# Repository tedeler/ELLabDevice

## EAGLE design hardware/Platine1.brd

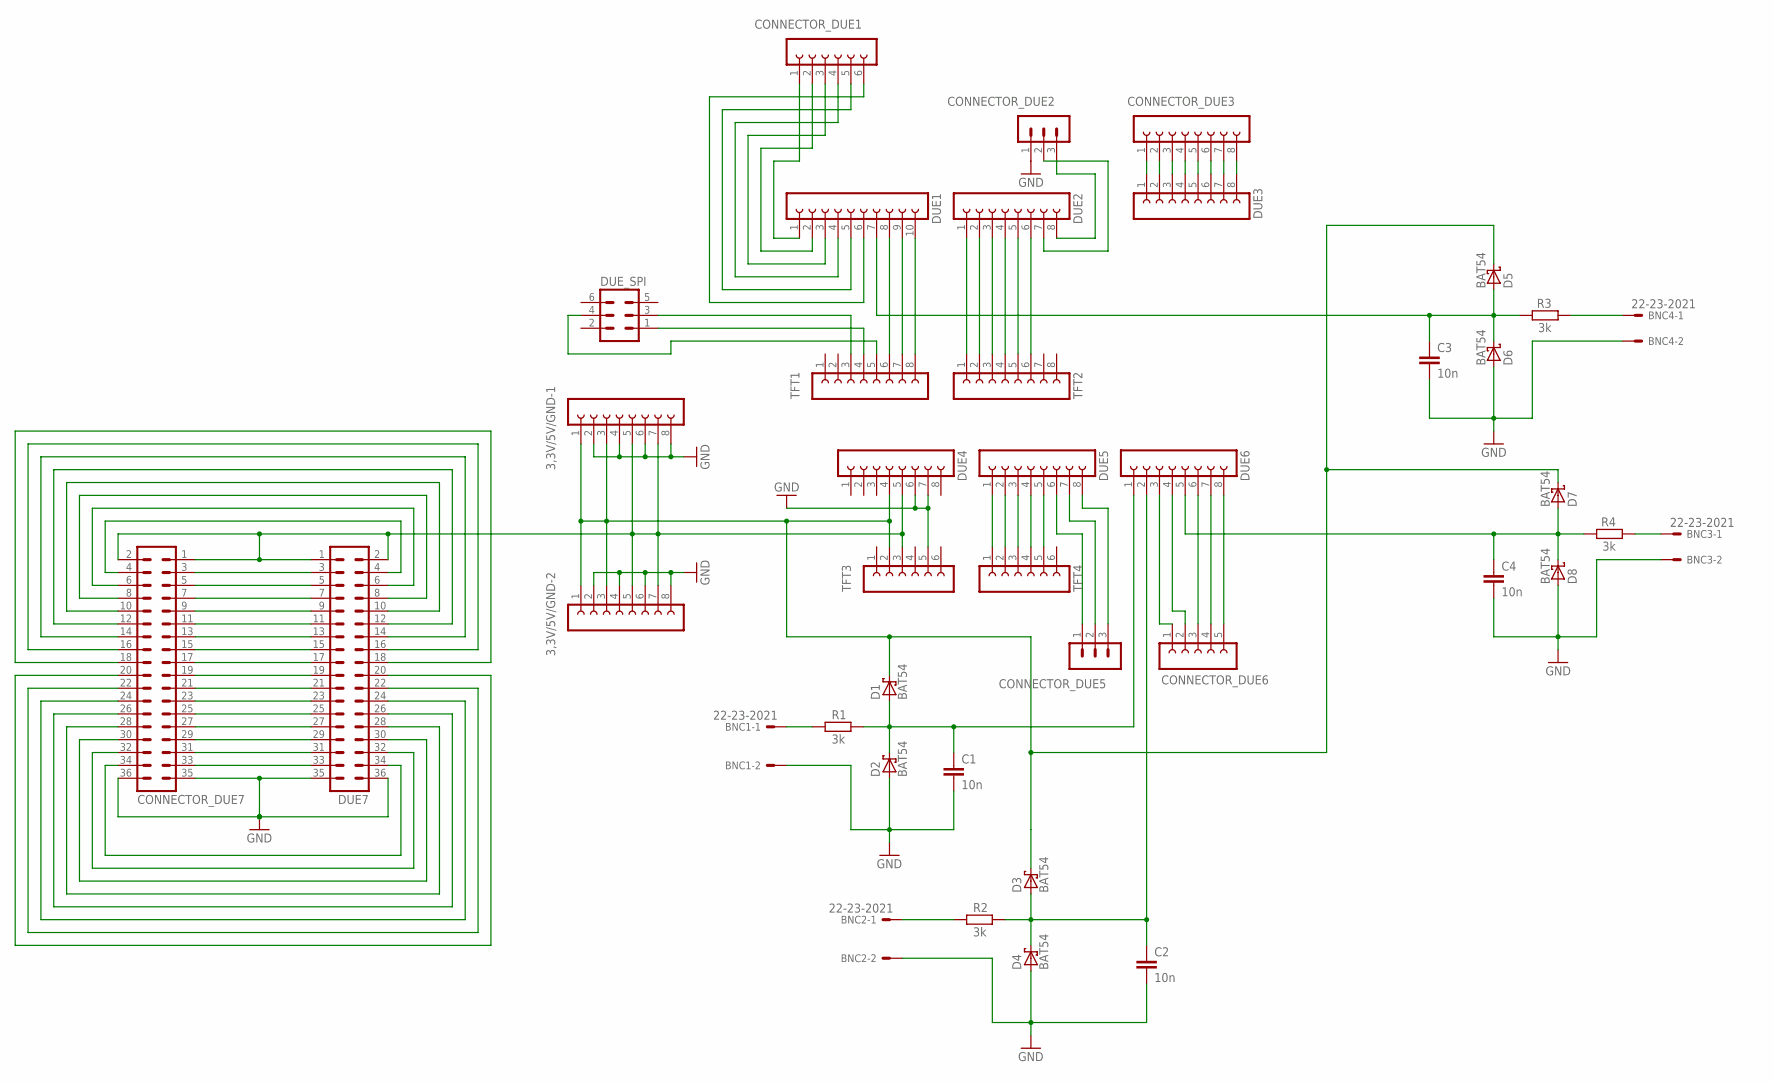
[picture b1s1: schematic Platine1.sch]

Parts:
3,3V/5V/GND-1, 3,3V/5V/GND-2: FE08-1; FE08
BNC1, BNC2, BNC3, BNC4: 22-23-2021
C1, C2, C3, C4: 10n; C025-024X044
CONNECTOR_DUE1: FE06-1; FE06
CONNECTOR_DUE2, CONNECTOR_DUE5: MA03-1
CONNECTOR_DUE3: FE08-1; FE08
CONNECTOR_DUE6: FE05-1
CONNECTOR_DUE7: MA18-2
D1, D2, D3, D4, D5, D6, D7, D8: BAT54; SOT23
DUE1: FE10-1; FE10
DUE2, DUE3, DUE4, DUE5, DUE6: FE08-1; FE08
DUE7: MA18-2
DUE_SPI: MA03-2
R1, R2, R3, R4: 3k; 0207/12
TFT1, TFT2: FE08-1; FE08
TFT3, TFT4: FE06-1; FE06

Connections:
GND: 3,3V/5V/GND-1.2, 3,3V/5V/GND-1.4, 3,3V/5V/GND-1.6, 3,3V/5V/GND-1.8, 3,3V/5V/GND-2.2, 3,3V/5V/GND-2.4, 3,3V/5V/GND-2.6, 3,3V/5V/GND-2.8, BNC1.2, BNC2.2, BNC3.2, BNC4.2, C1.2, C2.2, C3.2, C4.2, CONNECTOR_DUE2.1, CONNECTOR_DUE7.35, CONNECTOR_DUE7.36, D2.1 (A), D4.1 (A), D6.1 (A), D8.1 (A), DUE4.6, DUE4.7, DUE7.35, DUE7.36, TFT3.5
unnamed: C1.1, D1.1 (A), D2.3 (C), DUE6.1, R1.2
unnamed: C2.1, D3.1 (A), D4.3 (C), DUE6.2, R2.2
unnamed: BNC1.1, R1.1
unnamed: BNC2.1, R2.1
unnamed: DUE1.10, TFT1.8
unnamed: DUE1.9, TFT1.7
unnamed: DUE1.8, TFT1.6
unnamed: DUE_SPI.3, TFT1.3
unnamed: DUE_SPI.1, TFT1.4
unnamed: DUE_SPI.4, TFT1.5
unnamed: C3.1, D5.1 (A), D6.3 (C), DUE1.7, R3.2
unnamed: CONNECTOR_DUE3.1, DUE3.1
unnamed: DUE2.1, TFT2.1
unnamed: DUE2.2, TFT2.2
unnamed: DUE2.3, TFT2.3
unnamed: DUE2.4, TFT2.4
unnamed: DUE2.5, TFT2.5
unnamed: DUE2.6, TFT2.6
unnamed: CONNECTOR_DUE7.3, DUE7.3
unnamed: CONNECTOR_DUE7.5, DUE7.5
unnamed: CONNECTOR_DUE7.7, DUE7.7
unnamed: BNC4.1, R3.1
unnamed: C4.1, D7.1 (A), D8.3 (C), DUE6.5, R4.2
unnamed: CONNECTOR_DUE7.9, DUE7.9
unnamed: BNC3.1, R4.1
unnamed: DUE5.1, TFT4.1
unnamed: DUE5.2, TFT4.2
unnamed: DUE5.3, TFT4.3
unnamed: DUE5.4, TFT4.4
unnamed: DUE5.5, TFT4.5
unnamed: CONNECTOR_DUE7.11, DUE7.11
unnamed: CONNECTOR_DUE7.13, DUE7.13
unnamed: CONNECTOR_DUE7.15, DUE7.15
unnamed: CONNECTOR_DUE7.17, DUE7.17
unnamed: CONNECTOR_DUE7.19, DUE7.19
unnamed: CONNECTOR_DUE7.21, DUE7.21
unnamed: CONNECTOR_DUE7.23, DUE7.23
unnamed: CONNECTOR_DUE7.25, DUE7.25
unnamed: CONNECTOR_DUE7.27, DUE7.27
unnamed: CONNECTOR_DUE7.29, DUE7.29
unnamed: CONNECTOR_DUE7.31, DUE7.31
unnamed: CONNECTOR_DUE7.33, DUE7.33
unnamed: CONNECTOR_DUE7.34, DUE7.34
unnamed: CONNECTOR_DUE7.32, DUE7.32
unnamed: CONNECTOR_DUE7.4, DUE7.4
unnamed: CONNECTOR_DUE7.6, DUE7.6
unnamed: CONNECTOR_DUE7.8, DUE7.8
unnamed: CONNECTOR_DUE7.10, DUE7.10
unnamed: CONNECTOR_DUE7.12, DUE7.12
unnamed: CONNECTOR_DUE7.14, DUE7.14
unnamed: CONNECTOR_DUE7.16, DUE7.16
unnamed: CONNECTOR_DUE7.18, DUE7.18
unnamed: CONNECTOR_DUE7.30, DUE7.30
unnamed: CONNECTOR_DUE7.28, DUE7.28
unnamed: CONNECTOR_DUE7.26, DUE7.26
unnamed: CONNECTOR_DUE7.24, DUE7.24
unnamed: CONNECTOR_DUE7.22, DUE7.22
unnamed: CONNECTOR_DUE7.20, DUE7.20
unnamed: CONNECTOR_DUE3.2, DUE3.2
unnamed: CONNECTOR_DUE3.3, DUE3.3
unnamed: CONNECTOR_DUE3.4, DUE3.4
unnamed: CONNECTOR_DUE3.5, DUE3.5
unnamed: CONNECTOR_DUE3.6, DUE3.6
unnamed: CONNECTOR_DUE3.7, DUE3.7
unnamed: CONNECTOR_DUE3.8, DUE3.8
unnamed: CONNECTOR_DUE1.1, DUE1.1
unnamed: CONNECTOR_DUE1.2, DUE1.2
unnamed: CONNECTOR_DUE1.3, DUE1.3
unnamed: CONNECTOR_DUE1.4, DUE1.4
unnamed: CONNECTOR_DUE1.5, DUE1.5
unnamed: CONNECTOR_DUE1.6, DUE1.6
unnamed: CONNECTOR_DUE2.3, DUE2.8
unnamed: CONNECTOR_DUE2.2, DUE2.7
unnamed: CONNECTOR_DUE5.1, DUE5.6
unnamed: CONNECTOR_DUE5.2, DUE5.7
unnamed: CONNECTOR_DUE5.3, DUE5.8
unnamed: CONNECTOR_DUE6.1, DUE6.3
unnamed: CONNECTOR_DUE6.2, DUE6.4
unnamed: CONNECTOR_DUE6.3, DUE6.6
unnamed: CONNECTOR_DUE6.4, DUE6.7
unnamed: CONNECTOR_DUE6.5, DUE6.8
unnamed: 3,3V/5V/GND-1.1, 3,3V/5V/GND-1.3, 3,3V/5V/GND-2.1, 3,3V/5V/GND-2.3, D1.3 (C), D5.3 (C), D7.3 (C), DUE4.4, TFT3.2
unnamed: 3,3V/5V/GND-1.5, 3,3V/5V/GND-1.7, 3,3V/5V/GND-2.5, 3,3V/5V/GND-2.7, CONNECTOR_DUE7.1, CONNECTOR_DUE7.2, DUE4.5, DUE7.1, DUE7.2, TFT3.3

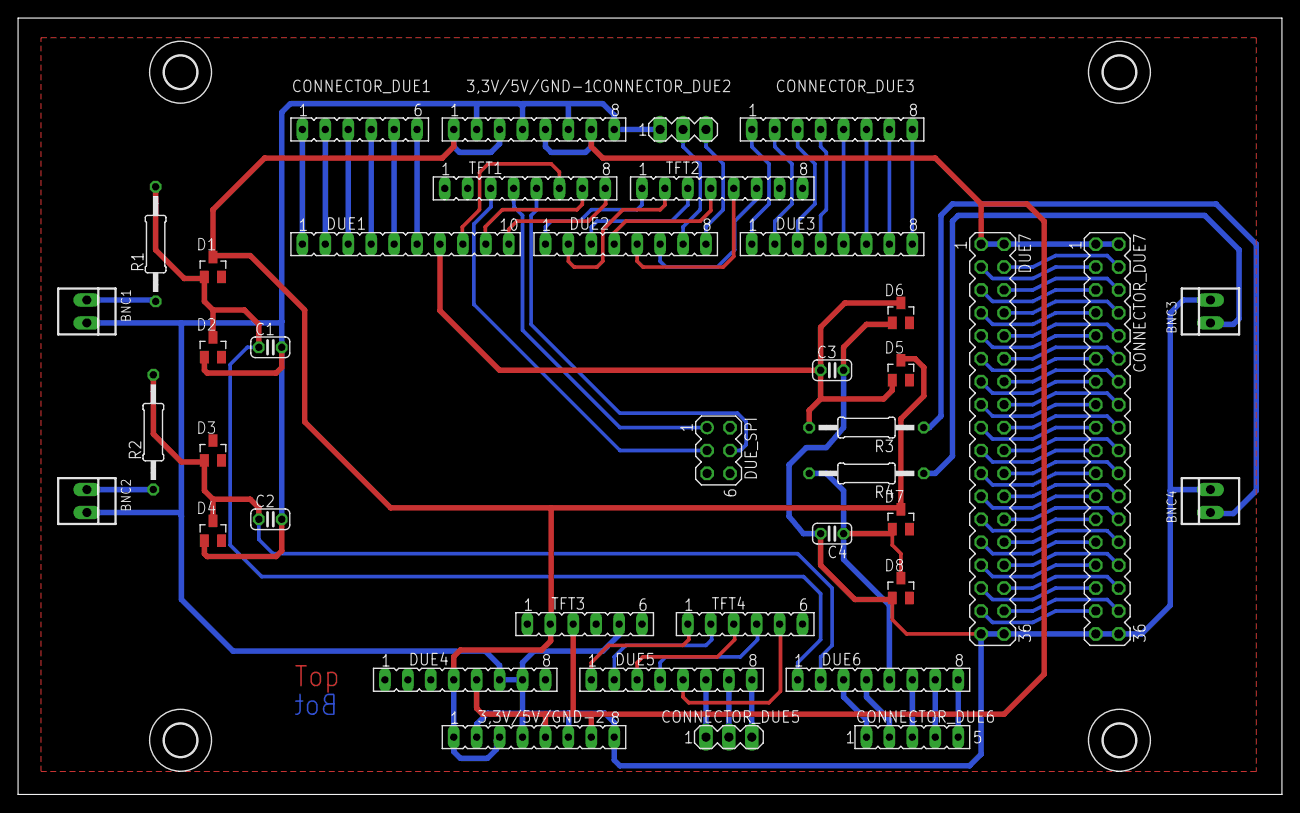
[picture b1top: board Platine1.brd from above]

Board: 2 copper layers, 140.0 x 86.0 mm, 44 parts (0 on the bottom side), 84 nets.

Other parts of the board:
U$5, U$6, U$7, U$8: 3,6

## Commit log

2019-09-26 Init
2019-09-26 Dateien verschoben
2019-09-26 Eclipse Projekt angelegt und Namen geändert
2019-09-26 Deleted Release Files
2019-09-26 Release ignore
2019-09-27 Uploadeinstellungen für Programming Port
2019-09-27 Code Restrukturiert (alpha)
2019-09-27 Alles rausgeworfen, bis auf Labor1
2019-09-27 Einiges umbenannt
2019-09-27 Alte Version rausgeworfen
2019-09-27 Startbildschirm ist jetzt eigene App.
    Es erfolgt keine Verwendung von new und delete mehr. Das ist jetzt über init() und done() Methoden gelöst, ohne dass das Objekt aus dem Speicher verschwindet.
2019-09-29 Momentan noch Bildstörungen durch konkurrierenden Zugriff aus der ISR (auf touch) und der Hauptschleife (auf das Display).
2019-09-29 160us -> 140us für getPoint
2019-09-29 50us Aber jetzt funktioniert touch nur noch sporadisch.
2019-10-01 deleted slobber files
2019-10-01 Moved files to src folder
2019-10-01 Platformio files
2019-10-02 Faster Display refresh through correct ADC-Handler acknowledge
2019-10-16 Rotary Switch ist jetzt Flankenbasiert (steigend) Umstellung auf Due Native-Port
2019-10-16 Mittelwertberechnung hinzugefügt Anzeige verbessert
